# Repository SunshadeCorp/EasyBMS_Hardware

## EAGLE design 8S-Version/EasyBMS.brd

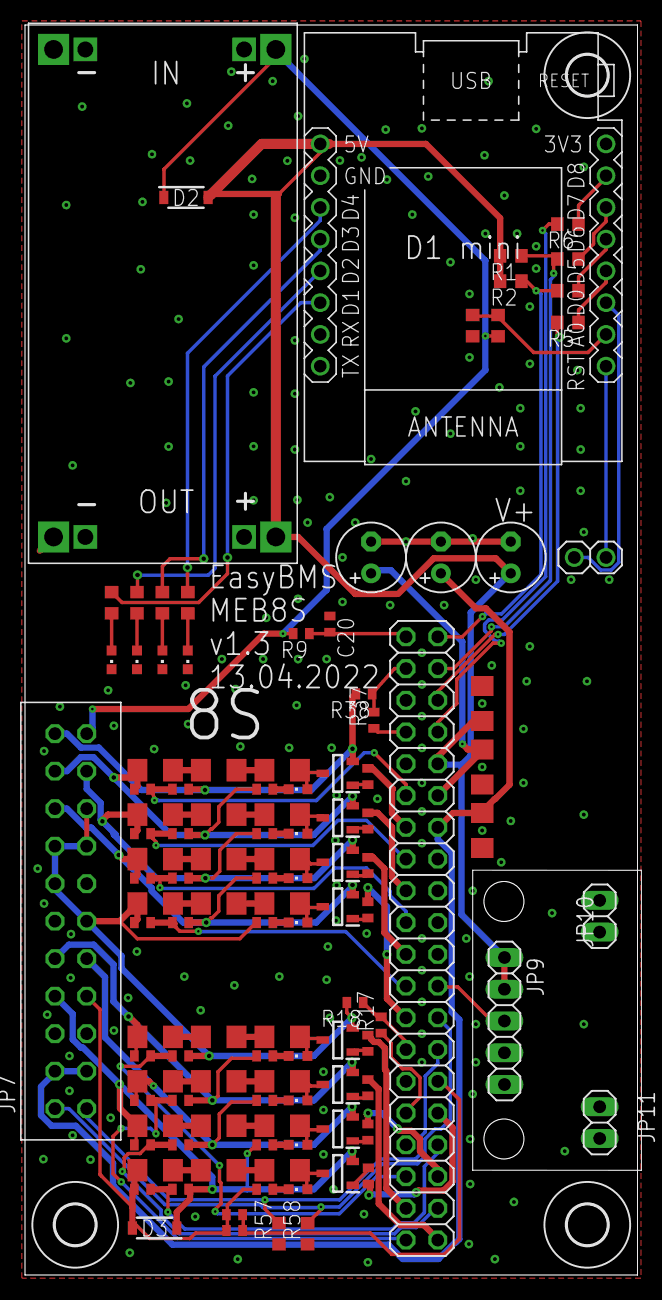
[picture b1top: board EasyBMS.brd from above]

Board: 2 copper layers, 49.0 x 100.0 mm, 117 parts (0 on the bottom side), 98 nets.

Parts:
C1, C2, C3: 1uF; E2,5-6
C4, C18, C19: 100nF; C1206
C5, C6, C7, C8, C9, C12, C13, C14, C15: 10nF; C0402
C20: 100n; C0402
D2, D3: SM4007PL-TP; SODFL3616X135N
H1, H2, H3: MOUNT-HOLE3.2; 3,2
JP3, JP10, JP11: 1X02
JP5: 2X20
JP7: 2X11_MEB12S
JP9: 1X05
LED1, LED2, LED3, LED4, LED5, LED6, LED7, LED8, LED12, LED13, LED14, LED15: KT-0603R; CHIPLED_0603
Q2, Q3, Q4, Q5, Q8, Q9, Q10, Q11: BSS84LT1G; SOT96P237X111-3N
R1, R2: 5K1; R0603
R3, R9, R12, R18, R24, R30, R36, R38, R64, R70, R76, R83: 100R; R0402
R4, R7, R8, R14, R20, R21, R25, R26, R27, R31, R32, R33, R49, R50, R51, R65, R66, R67, R71, R72, R73, R77, R78, R79: 10R0; R1206
R5, R6, R61, R62: 1k; R0603
R10, R22, R28, R34, R52, R68, R74, R80: 3.3k; R0402
R11, R23, R29, R35, R63, R69, R75, R81: 470R; R0402
R15: 470k; R0603
R16: 27K; R0603
R17, R37: 0R; R0402
R53, R54, R55, R56: 200R0; R0603
R57, R58: 12k; R0603
U$1: DC-DC-STEP-DOWN-LM2596HVS
U$2: WEMOS-D1-MINI

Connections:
5VDC: C3.+, C19.1, D2.2, JP5.10, JP9.1, JP9.2, R1.2, R2.2, U$1.OUT+, U$2.JP2.8
A0IN: R15.1, R16.2, U$2.JP1.2
C0: C5.1, JP5.30, R3.1
C1: C6.1, JP5.34, R12.1
C1+: C7.2, D3.1, JP7.16_C1+, Q2.2, R12.2, R14.1, R23.2
C1-: C5.2, C6.2, D3.2, JP7.15_TOTAL-, R3.2, R4.1, R11.2
C2: C7.1, JP5.38, R24.1
C2+: C9.2, JP7.13_C2+, Q3.2, R24.2, R31.1, R35.2
C3: C9.1, JP5.39, R36.1
C3+: C8.2, JP7.14_C3+, Q5.2, R25.1, R29.2, R36.2
C4: C8.1, JP5.35, R30.1
C4+: C12.2, JP7.5_C8+, JP7.7_C6+, JP7.8_C7+, JP7.10_C5+, JP7.11_C4+, Q4.2, R18.2, R30.2, R49.1, R63.2
C5: JP5.31, R17.1
C5+: C13.2, JP7.6_C9+, Q8.2, R64.2, R65.1, R69.2
C6: JP5.27, R17.2, R18.1
C6+: C14.2, JP7.3_C10+, Q9.2, R70.2, R71.1, R75.2
C7: C12.1, JP5.23, R64.1
C7+: C15.2, JP7.4_C11+, Q10.2, R76.2, R77.1, R81.2
C8: C13.1, JP5.19, R70.1
C8+: JP7.2_TOTAL+2, Q11.2, R38.2, R83.2
C9: C14.1, JP5.15, R76.1
C10: C15.1, JP5.11, R83.1
C11: JP5.7, R37.1
C12: JP5.3, R37.2, R38.1
CSB: JP5.8, R6.2
GND: C1.-, C2.-, C3.-, C4.2, C18.2, C19.2, C20.1, JP5.16, JP5.18, JP7.17_TOTAL-, JP9.4, JP9.5, JP10.1, JP10.2, JP11.1, JP11.2, LED1.C, LED2.C, LED3.C, LED4.C, R16.1, R57.1, R58.1, U$1.IN-, U$1.OUT-, U$2.JP2.7
ISIGNAL: JP5.24, JP9.3
MISO: JP5.2, R2.1, R61.2
MOSI: JP5.4, R1.1, R62.2
unnamed: LED1.A, R53.1
unnamed: LED2.A, R54.1
unnamed: LED3.A, R55.1
unnamed: LED4.A, R56.1
unnamed: JP3.2, U$2.JP1.1
unnamed: JP3.1, U$2.JP1.3
unnamed: R5.1, U$2.JP1.4
unnamed: R4.2, R7.1
unnamed: R7.2, R8.1
unnamed: LED5.A, Q2.3, R8.2
unnamed: Q2.1, R10.2
unnamed: LED5.C, R11.1
unnamed: R14.2, R20.1
unnamed: R20.2, R21.1
unnamed: R6.1, U$2.JP1.7
unnamed: LED6.A, Q3.3, R21.2
unnamed: Q3.1, R22.2
unnamed: LED6.C, R23.1
unnamed: R25.2, R26.1
unnamed: R26.2, R27.1
unnamed: LED7.A, Q4.3, R27.2
unnamed: Q4.1, R28.2
unnamed: LED7.C, R29.1
unnamed: R31.2, R32.1
unnamed: R32.2, R33.1
unnamed: LED8.A, Q5.3, R33.2
unnamed: R56.2, U$2.JP2.6
unnamed: Q5.1, R34.2
unnamed: LED8.C, R35.1
unnamed: R49.2, R50.1
unnamed: R50.2, R51.1
unnamed: LED12.A, Q8.3, R51.2
unnamed: Q8.1, R52.2
unnamed: LED12.C, R63.1
unnamed: R65.2, R66.1
unnamed: R66.2, R67.1
unnamed: LED13.A, Q9.3, R67.2
unnamed: Q9.1, R68.2
unnamed: LED13.C, R69.1
unnamed: R71.2, R72.1
unnamed: R72.2, R73.1
unnamed: LED14.A, Q10.3, R73.2
unnamed: Q10.1, R74.2
unnamed: LED14.C, R75.1
unnamed: R77.2, R78.1
unnamed: R78.2, R79.1
unnamed: LED15.A, Q11.3, R79.2
unnamed: Q11.1, R80.2
unnamed: LED15.C, R81.1
unnamed: R53.2, U$2.JP2.3
unnamed: R61.1, U$2.JP1.5
unnamed: R62.1, U$2.JP1.6
unnamed: R55.2, U$2.JP2.5
unnamed: R54.2, U$2.JP2.4
S1: JP5.32, R10.1
S2: JP5.36, R22.1
S3: JP5.40, R34.1
S4: JP5.37, R28.1
S7: JP5.25, R52.1
S8: JP5.21, R68.1
S9: JP5.17, R74.1
S10: JP5.13, R80.1
SCK: JP5.6, R5.2
V+: C20.2, JP5.1, R9.1
VIN: D2.1, JP7.1_TOTAL+, R9.2, R15.2, U$1.IN+
VREF1: C1.+, C18.1, JP5.12
VREF2: C2.+, C4.1, JP5.14, JP7.19_THERMO1_IN, JP7.20_THERMO2_IN
VTEMP1: JP5.28, JP7.21_THERMO1_OUT, R57.2
VTEMP2: JP5.26, JP7.22_THERMO2_OUT, R58.2

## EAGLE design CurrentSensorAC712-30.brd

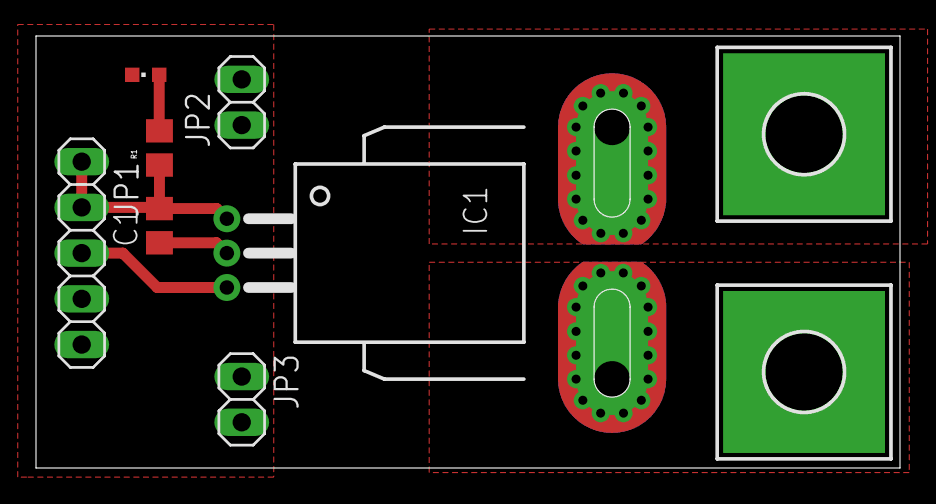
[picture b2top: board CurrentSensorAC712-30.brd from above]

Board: 2 copper layers, 48.0 x 24.0 mm, 9 parts (0 on the bottom side), 6 nets.

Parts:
C1: 100nF; C0805
H1, H2: MOUNT-PAD-SQUARE4.3; 4,3-PAD-SQUARE
IC1: ACS758LCB-050B-PFF-T; CB-PFF
JP1: 1X05
JP2, JP3: 1X02
LED1: KT-0603R; CHIPLED_0603
R1: 1k; R0805

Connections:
5VDC: C1.2, IC1.1, JP1.1, JP1.2, R1.1
GND: C1.1, IC1.2, JP1.4, JP1.5, JP2.1, JP2.2, JP3.1, JP3.2, LED1.C
IN: H1.B4,3, IC1.IP+, IC1.IP+@2, IC1.IP+@3, IC1.IP+@4, IC1.IP+@5, IC1.IP+@6, IC1.IP+@7, IC1.IP+@8, IC1.IP+@9, IC1.IP+@10, IC1.IP+@11, IC1.IP+@12, IC1.IP+@13, IC1.IP+@14, IC1.IP+@15, IC1.IP+@16, IC1.IP+@17
unnamed: LED1.A, R1.2
unnamed: IC1.3, JP1.3
OUT: H2.B4,3, IC1.IP-, IC1.IP-@2, IC1.IP-@3, IC1.IP-@4, IC1.IP-@5, IC1.IP-@6, IC1.IP-@7, IC1.IP-@8, IC1.IP-@9, IC1.IP-@10, IC1.IP-@11, IC1.IP-@12, IC1.IP-@13, IC1.IP-@14, IC1.IP-@15, IC1.IP-@16, IC1.IP-@17

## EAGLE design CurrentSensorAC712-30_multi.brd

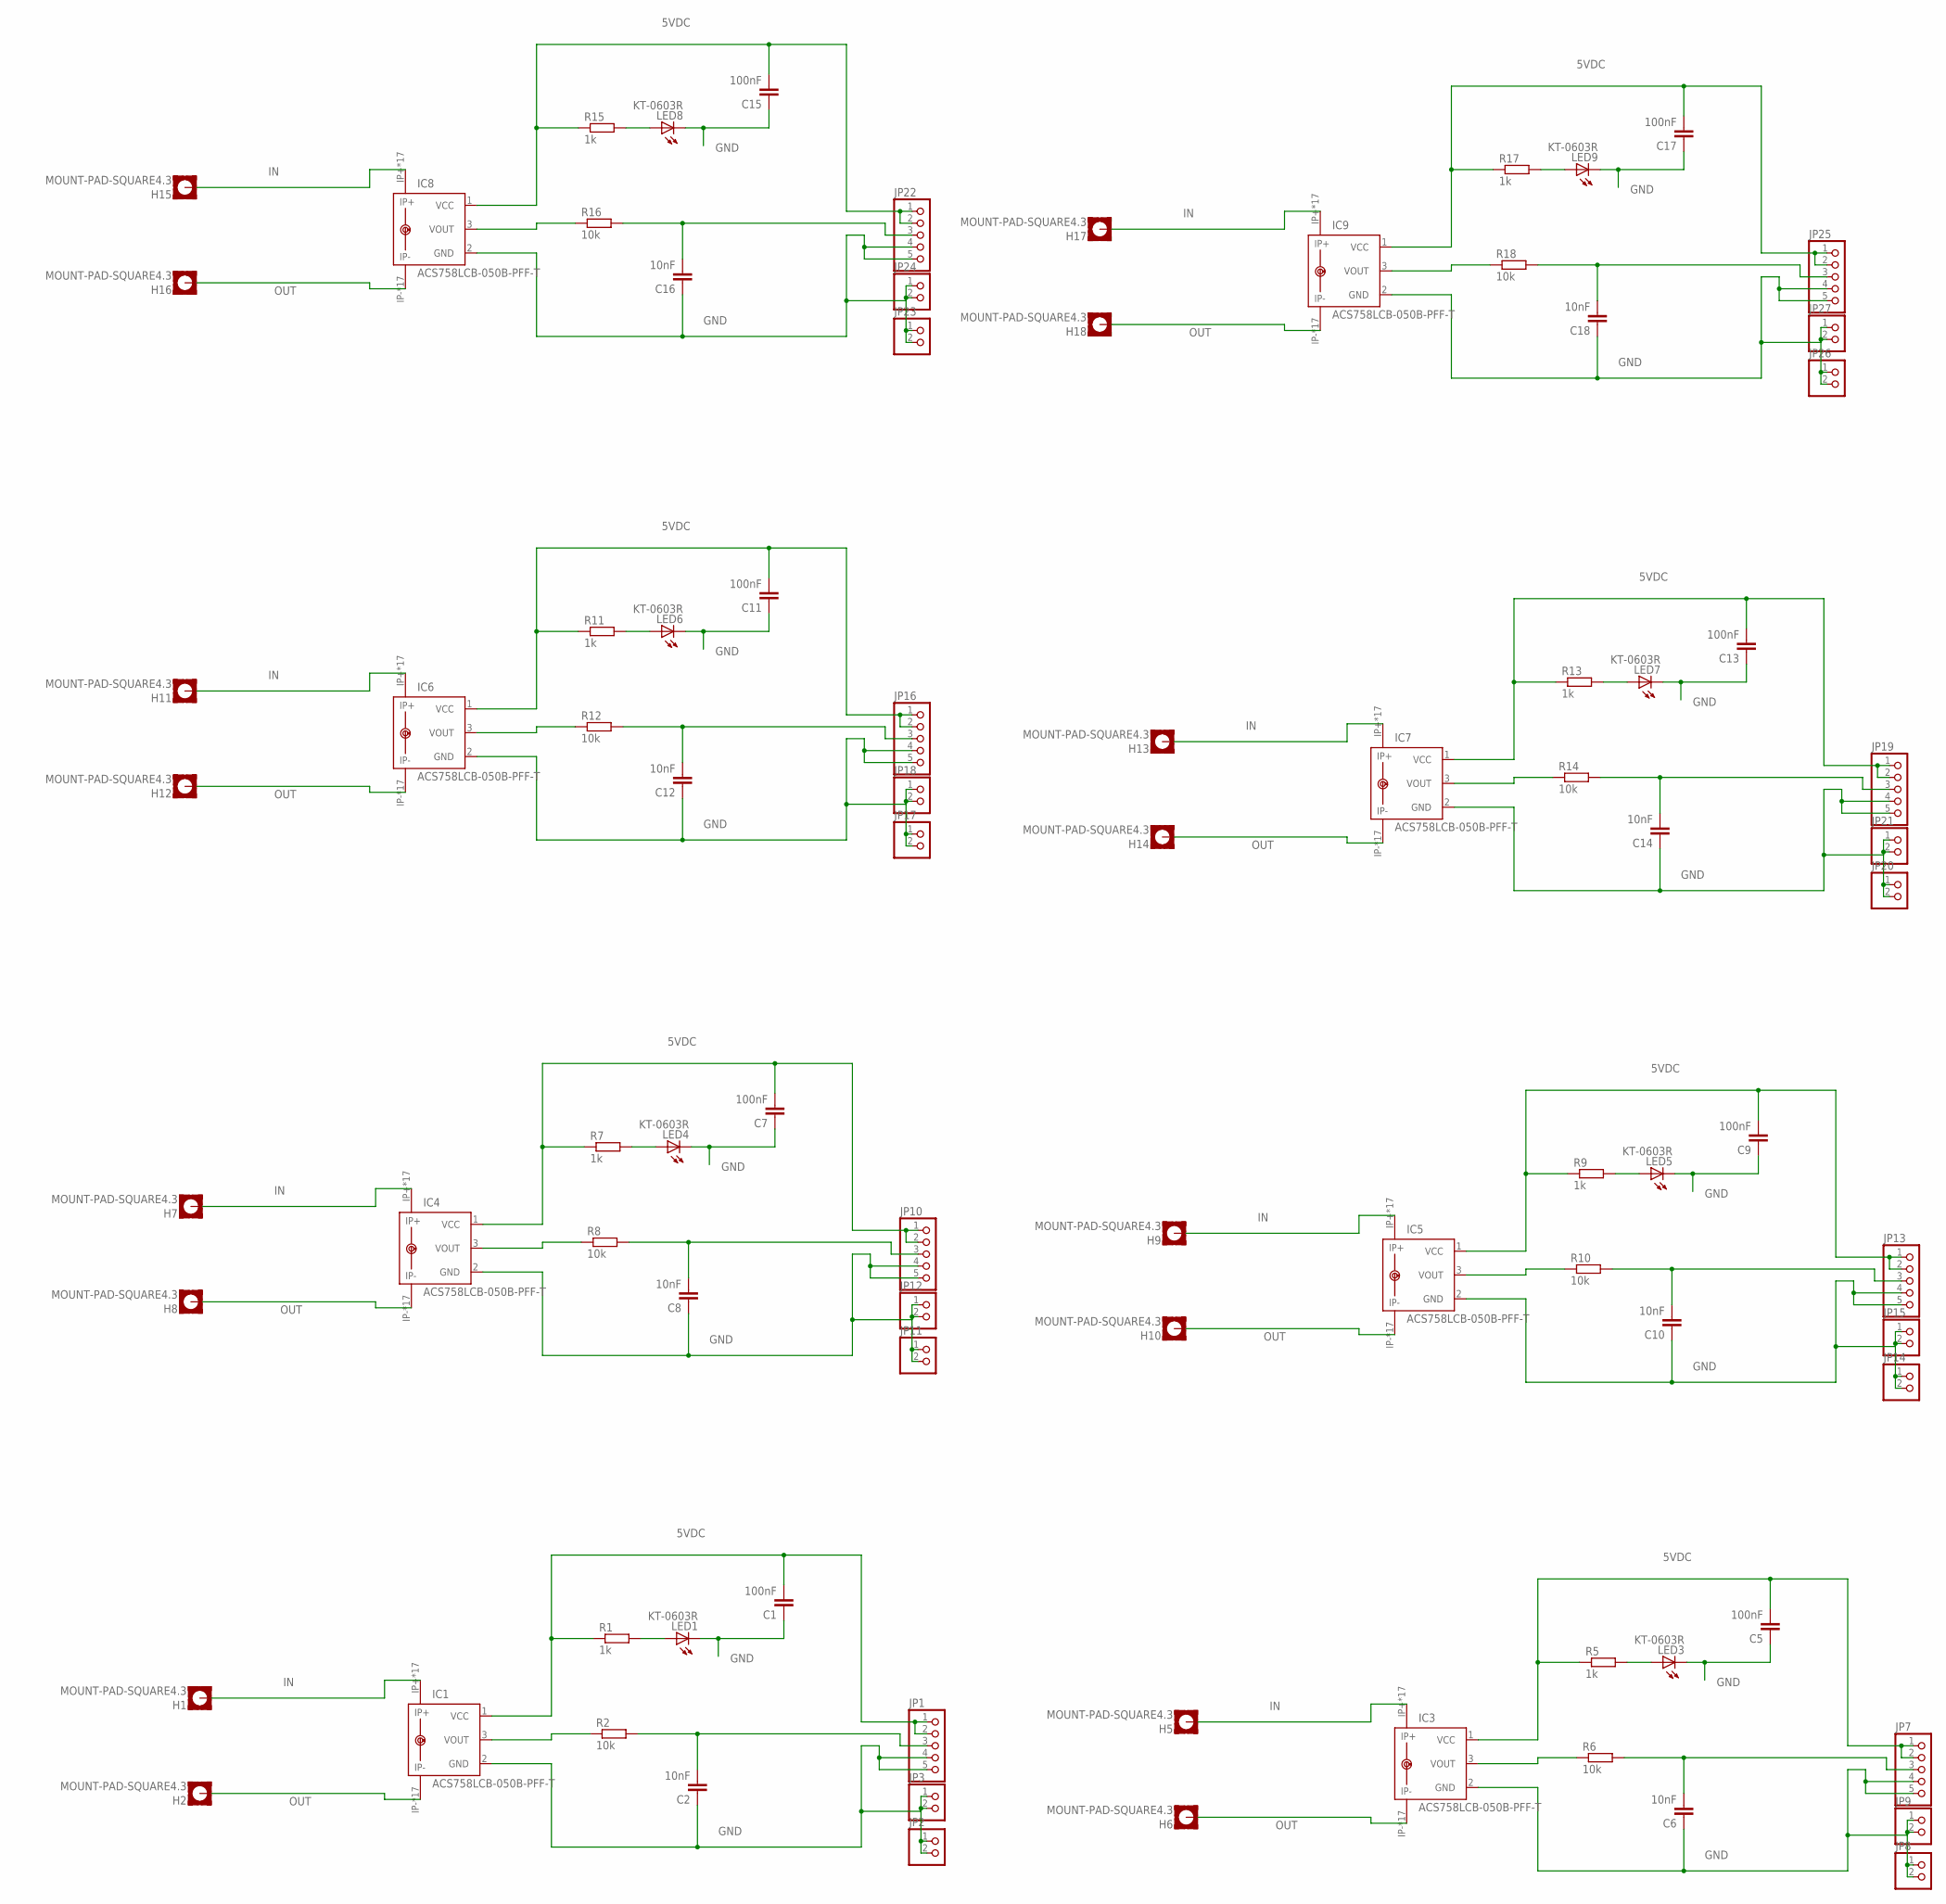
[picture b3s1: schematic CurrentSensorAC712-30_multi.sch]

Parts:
C1, C5, C7, C9, C11, C13, C15, C17: 100nF; C0805
C2, C6, C8, C10, C12, C14, C16, C18: 10nF; C0805
H1, H2, H5, H6, H7, H8, H9, H10, H11, H12, H13, H14, H15, H16, H17, H18: MOUNT-PAD-SQUARE4.3; 4,3-PAD-SQUARE
IC1, IC3, IC4, IC5, IC6, IC7, IC8, IC9: ACS758LCB-050B-PFF-T; CB-PFF
JP1, JP7, JP10, JP13, JP16, JP19, JP22, JP25: PINHD-1X5; 1X05
JP2, JP3, JP8, JP9, JP11, JP12, JP14, JP15, JP17, JP18, JP20, JP21, JP23, JP24, JP26, JP27: PINHD-1X2; 1X02
LED1, LED3, LED4, LED5, LED6, LED7, LED8, LED9: KT-0603R; CHIPLED_0603
R1, R5, R7, R9, R11, R13, R15, R17: 1k; R0805
R2, R6, R8, R10, R12, R14, R16, R18: 10k; R0805

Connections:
5VDC: C1.2, C5.2, C7.2, C9.2, C11.2, C13.2, C15.2, C17.2, IC1.1 (VCC), IC3.1 (VCC), IC4.1 (VCC), IC5.1 (VCC), IC6.1 (VCC), IC7.1 (VCC), IC8.1 (VCC), IC9.1 (VCC), JP1.1, JP1.2, JP7.1, JP7.2, JP10.1, JP10.2, JP13.1, JP13.2, JP16.1, JP16.2, JP19.1, JP19.2, JP22.1, JP22.2, JP25.1, JP25.2, R1.1, R5.1, R7.1, R9.1, R11.1, R13.1, R15.1, R17.1
GND: C1.1, C2.1, C5.1, C6.1, C7.1, C8.1, C9.1, C10.1, C11.1, C12.1, C13.1, C14.1, C15.1, C16.1, C17.1, C18.1, IC1.2 (GND), IC3.2 (GND), IC4.2 (GND), IC5.2 (GND), IC6.2 (GND), IC7.2 (GND), IC8.2 (GND), IC9.2 (GND), JP1.4, JP1.5, JP2.1, JP2.2, JP3.1, JP3.2, JP7.4, JP7.5, JP8.1, JP8.2, JP9.1, JP9.2, JP10.4, JP10.5, JP11.1, JP11.2, JP12.1, JP12.2, JP13.4, JP13.5, JP14.1, JP14.2, JP15.1, JP15.2, JP16.4, JP16.5, JP17.1, JP17.2, JP18.1, JP18.2, JP19.4, JP19.5, JP20.1, JP20.2, JP21.1, JP21.2, JP22.4, JP22.5, JP23.1, JP23.2, JP24.1, JP24.2, JP25.4, JP25.5, JP26.1, JP26.2, JP27.1, JP27.2, LED1.C, LED3.C, LED4.C, LED5.C, LED6.C, LED7.C, LED8.C, LED9.C
IN: H1.B4,3, H5.B4,3, H7.B4,3, H9.B4,3, H11.B4,3, H13.B4,3, H15.B4,3, H17.B4,3, IC1.IP+, IC1.IP+@2 (IP+), IC1.IP+@3 (IP+), IC1.IP+@4 (IP+), IC1.IP+@5 (IP+), IC1.IP+@6 (IP+), IC1.IP+@7 (IP+), IC1.IP+@8 (IP+), IC1.IP+@9 (IP+), IC1.IP+@10 (IP+), IC1.IP+@11 (IP+), IC1.IP+@12 (IP+), IC1.IP+@13 (IP+), IC1.IP+@14 (IP+), IC1.IP+@15 (IP+), IC1.IP+@16 (IP+), IC1.IP+@17 (IP+), IC3.IP+, IC3.IP+@2 (IP+), IC3.IP+@3 (IP+), IC3.IP+@4 (IP+), IC3.IP+@5 (IP+), IC3.IP+@6 (IP+), IC3.IP+@7 (IP+), IC3.IP+@8 (IP+), IC3.IP+@9 (IP+), IC3.IP+@10 (IP+), IC3.IP+@11 (IP+), IC3.IP+@12 (IP+), IC3.IP+@13 (IP+), IC3.IP+@14 (IP+), IC3.IP+@15 (IP+), IC3.IP+@16 (IP+), IC3.IP+@17 (IP+), IC4.IP+, IC4.IP+@2 (IP+), IC4.IP+@3 (IP+), IC4.IP+@4 (IP+), IC4.IP+@5 (IP+), IC4.IP+@6 (IP+), IC4.IP+@7 (IP+), IC4.IP+@8 (IP+), IC4.IP+@9 (IP+), IC4.IP+@10 (IP+), IC4.IP+@11 (IP+), IC4.IP+@12 (IP+), IC4.IP+@13 (IP+), IC4.IP+@14 (IP+), IC4.IP+@15 (IP+), IC4.IP+@16 (IP+), IC4.IP+@17 (IP+), IC5.IP+, IC5.IP+@2 (IP+), IC5.IP+@3 (IP+), IC5.IP+@4 (IP+), IC5.IP+@5 (IP+), IC5.IP+@6 (IP+), IC5.IP+@7 (IP+), IC5.IP+@8 (IP+), IC5.IP+@9 (IP+), IC5.IP+@10 (IP+), IC5.IP+@11 (IP+), IC5.IP+@12 (IP+), IC5.IP+@13 (IP+), IC5.IP+@14 (IP+), IC5.IP+@15 (IP+), IC5.IP+@16 (IP+), IC5.IP+@17 (IP+), IC6.IP+, IC6.IP+@2 (IP+), IC6.IP+@3 (IP+), IC6.IP+@4 (IP+), IC6.IP+@5 (IP+), IC6.IP+@6 (IP+), IC6.IP+@7 (IP+), IC6.IP+@8 (IP+), IC6.IP+@9 (IP+), IC6.IP+@10 (IP+), IC6.IP+@11 (IP+), IC6.IP+@12 (IP+), IC6.IP+@13 (IP+), IC6.IP+@14 (IP+), IC6.IP+@15 (IP+), IC6.IP+@16 (IP+), IC6.IP+@17 (IP+), IC7.IP+, IC7.IP+@2 (IP+), IC7.IP+@3 (IP+), IC7.IP+@4 (IP+), IC7.IP+@5 (IP+), IC7.IP+@6 (IP+), IC7.IP+@7 (IP+), IC7.IP+@8 (IP+), IC7.IP+@9 (IP+), IC7.IP+@10 (IP+), IC7.IP+@11 (IP+), IC7.IP+@12 (IP+), IC7.IP+@13 (IP+), IC7.IP+@14 (IP+), IC7.IP+@15 (IP+), IC7.IP+@16 (IP+), IC7.IP+@17 (IP+), IC8.IP+, IC8.IP+@2 (IP+), IC8.IP+@3 (IP+), IC8.IP+@4 (IP+), IC8.IP+@5 (IP+), IC8.IP+@6 (IP+), IC8.IP+@7 (IP+), IC8.IP+@8 (IP+), IC8.IP+@9 (IP+), IC8.IP+@10 (IP+), IC8.IP+@11 (IP+), IC8.IP+@12 (IP+), IC8.IP+@13 (IP+), IC8.IP+@14 (IP+), IC8.IP+@15 (IP+), IC8.IP+@16 (IP+), IC8.IP+@17 (IP+), IC9.IP+, IC9.IP+@2 (IP+), IC9.IP+@3 (IP+), IC9.IP+@4 (IP+), IC9.IP+@5 (IP+), IC9.IP+@6 (IP+), IC9.IP+@7 (IP+), IC9.IP+@8 (IP+), IC9.IP+@9 (IP+), IC9.IP+@10 (IP+), IC9.IP+@11 (IP+), IC9.IP+@12 (IP+), IC9.IP+@13 (IP+), IC9.IP+@14 (IP+), IC9.IP+@15 (IP+), IC9.IP+@16 (IP+), IC9.IP+@17 (IP+)
unnamed: IC1.3 (VOUT), R2.1
unnamed: LED1.A, R1.2
unnamed: C2.2, JP1.3, R2.2
unnamed: LED3.A, R5.2
unnamed: C6.2, JP7.3, R6.2
unnamed: IC3.3 (VOUT), R6.1
unnamed: LED4.A, R7.2
unnamed: C8.2, JP10.3, R8.2
unnamed: IC4.3 (VOUT), R8.1
unnamed: LED5.A, R9.2
unnamed: C10.2, JP13.3, R10.2
unnamed: IC5.3 (VOUT), R10.1
unnamed: LED6.A, R11.2
unnamed: C12.2, JP16.3, R12.2
unnamed: IC6.3 (VOUT), R12.1
unnamed: LED7.A, R13.2
unnamed: C14.2, JP19.3, R14.2
unnamed: IC7.3 (VOUT), R14.1
unnamed: LED8.A, R15.2
unnamed: C16.2, JP22.3, R16.2
unnamed: IC8.3 (VOUT), R16.1
unnamed: LED9.A, R17.2
unnamed: C18.2, JP25.3, R18.2
unnamed: IC9.3 (VOUT), R18.1
OUT: H2.B4,3, H6.B4,3, H8.B4,3, H10.B4,3, H12.B4,3, H14.B4,3, H16.B4,3, H18.B4,3, IC1.IP-, IC1.IP-@2 (IP-), IC1.IP-@3 (IP-), IC1.IP-@4 (IP-), IC1.IP-@5 (IP-), IC1.IP-@6 (IP-), IC1.IP-@7 (IP-), IC1.IP-@8 (IP-), IC1.IP-@9 (IP-), IC1.IP-@10 (IP-), IC1.IP-@11 (IP-), IC1.IP-@12 (IP-), IC1.IP-@13 (IP-), IC1.IP-@14 (IP-), IC1.IP-@15 (IP-), IC1.IP-@16 (IP-), IC1.IP-@17 (IP-), IC3.IP-, IC3.IP-@2 (IP-), IC3.IP-@3 (IP-), IC3.IP-@4 (IP-), IC3.IP-@5 (IP-), IC3.IP-@6 (IP-), IC3.IP-@7 (IP-), IC3.IP-@8 (IP-), IC3.IP-@9 (IP-), IC3.IP-@10 (IP-), IC3.IP-@11 (IP-), IC3.IP-@12 (IP-), IC3.IP-@13 (IP-), IC3.IP-@14 (IP-), IC3.IP-@15 (IP-), IC3.IP-@16 (IP-), IC3.IP-@17 (IP-), IC4.IP-, IC4.IP-@2 (IP-), IC4.IP-@3 (IP-), IC4.IP-@4 (IP-), IC4.IP-@5 (IP-), IC4.IP-@6 (IP-), IC4.IP-@7 (IP-), IC4.IP-@8 (IP-), IC4.IP-@9 (IP-), IC4.IP-@10 (IP-), IC4.IP-@11 (IP-), IC4.IP-@12 (IP-), IC4.IP-@13 (IP-), IC4.IP-@14 (IP-), IC4.IP-@15 (IP-), IC4.IP-@16 (IP-), IC4.IP-@17 (IP-), IC5.IP-, IC5.IP-@2 (IP-), IC5.IP-@3 (IP-), IC5.IP-@4 (IP-), IC5.IP-@5 (IP-), IC5.IP-@6 (IP-), IC5.IP-@7 (IP-), IC5.IP-@8 (IP-), IC5.IP-@9 (IP-), IC5.IP-@10 (IP-), IC5.IP-@11 (IP-), IC5.IP-@12 (IP-), IC5.IP-@13 (IP-), IC5.IP-@14 (IP-), IC5.IP-@15 (IP-), IC5.IP-@16 (IP-), IC5.IP-@17 (IP-), IC6.IP-, IC6.IP-@2 (IP-), IC6.IP-@3 (IP-), IC6.IP-@4 (IP-), IC6.IP-@5 (IP-), IC6.IP-@6 (IP-), IC6.IP-@7 (IP-), IC6.IP-@8 (IP-), IC6.IP-@9 (IP-), IC6.IP-@10 (IP-), IC6.IP-@11 (IP-), IC6.IP-@12 (IP-), IC6.IP-@13 (IP-), IC6.IP-@14 (IP-), IC6.IP-@15 (IP-), IC6.IP-@16 (IP-), IC6.IP-@17 (IP-), IC7.IP-, IC7.IP-@2 (IP-), IC7.IP-@3 (IP-), IC7.IP-@4 (IP-), IC7.IP-@5 (IP-), IC7.IP-@6 (IP-), IC7.IP-@7 (IP-), IC7.IP-@8 (IP-), IC7.IP-@9 (IP-), IC7.IP-@10 (IP-), IC7.IP-@11 (IP-), IC7.IP-@12 (IP-), IC7.IP-@13 (IP-), IC7.IP-@14 (IP-), IC7.IP-@15 (IP-), IC7.IP-@16 (IP-), IC7.IP-@17 (IP-), IC8.IP-, IC8.IP-@2 (IP-), IC8.IP-@3 (IP-), IC8.IP-@4 (IP-), IC8.IP-@5 (IP-), IC8.IP-@6 (IP-), IC8.IP-@7 (IP-), IC8.IP-@8 (IP-), IC8.IP-@9 (IP-), IC8.IP-@10 (IP-), IC8.IP-@11 (IP-), IC8.IP-@12 (IP-), IC8.IP-@13 (IP-), IC8.IP-@14 (IP-), IC8.IP-@15 (IP-), IC8.IP-@16 (IP-), IC8.IP-@17 (IP-), IC9.IP-, IC9.IP-@2 (IP-), IC9.IP-@3 (IP-), IC9.IP-@4 (IP-), IC9.IP-@5 (IP-), IC9.IP-@6 (IP-), IC9.IP-@7 (IP-), IC9.IP-@8 (IP-), IC9.IP-@9 (IP-), IC9.IP-@10 (IP-), IC9.IP-@11 (IP-), IC9.IP-@12 (IP-), IC9.IP-@13 (IP-), IC9.IP-@14 (IP-), IC9.IP-@15 (IP-), IC9.IP-@16 (IP-), IC9.IP-@17 (IP-)

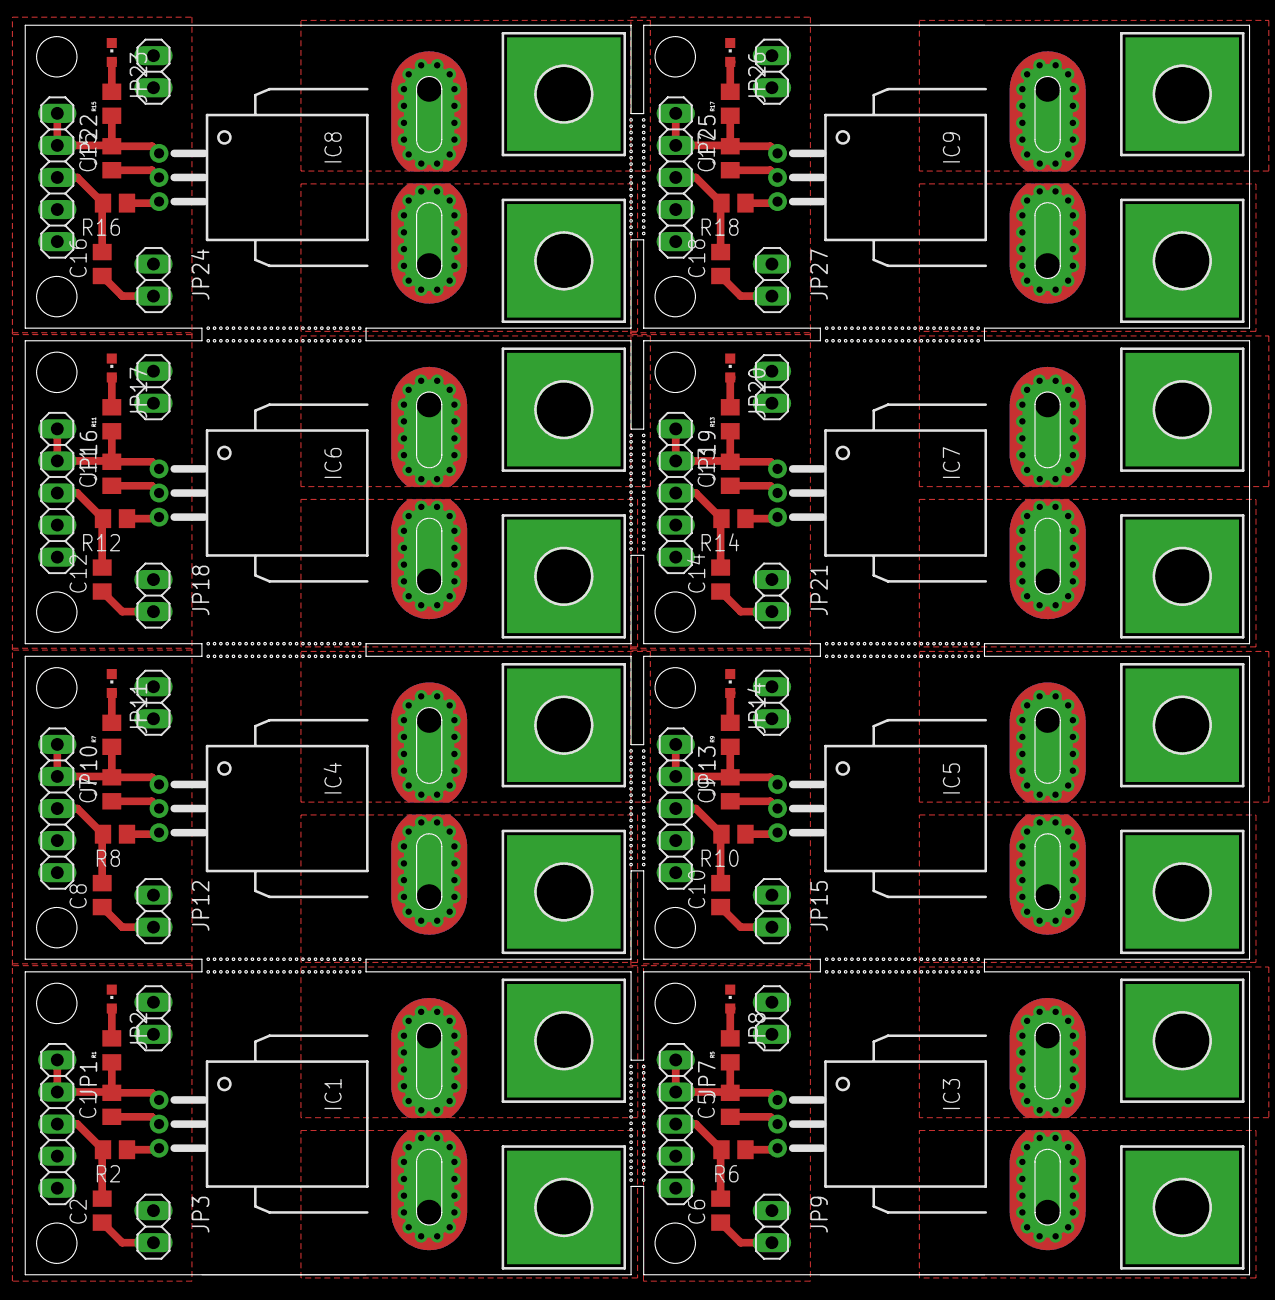
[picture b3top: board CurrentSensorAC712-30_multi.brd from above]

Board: 2 copper layers, 97.0 x 99.0 mm, 88 parts (0 on the bottom side), 28 nets.

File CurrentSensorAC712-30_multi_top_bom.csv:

Comment,Designator,Footprint,LCSC Part #
1k,R1 R5 R7 R9 R11 R13 R15 R17,R0805,
10k,R2 R6 R8 R10 R12 R14 R16 R18,R0805,
10nF,C2 C6 C8 C10 C12 C14 C16 C18,C0805,
100nF,C1 C5 C7 C9 C11 C13 C15 C17,C0805,
KT-0603R,LED1 LED3 LED4 LED5 LED6 LED7 LED8 LED9,CHIPLED_0603,

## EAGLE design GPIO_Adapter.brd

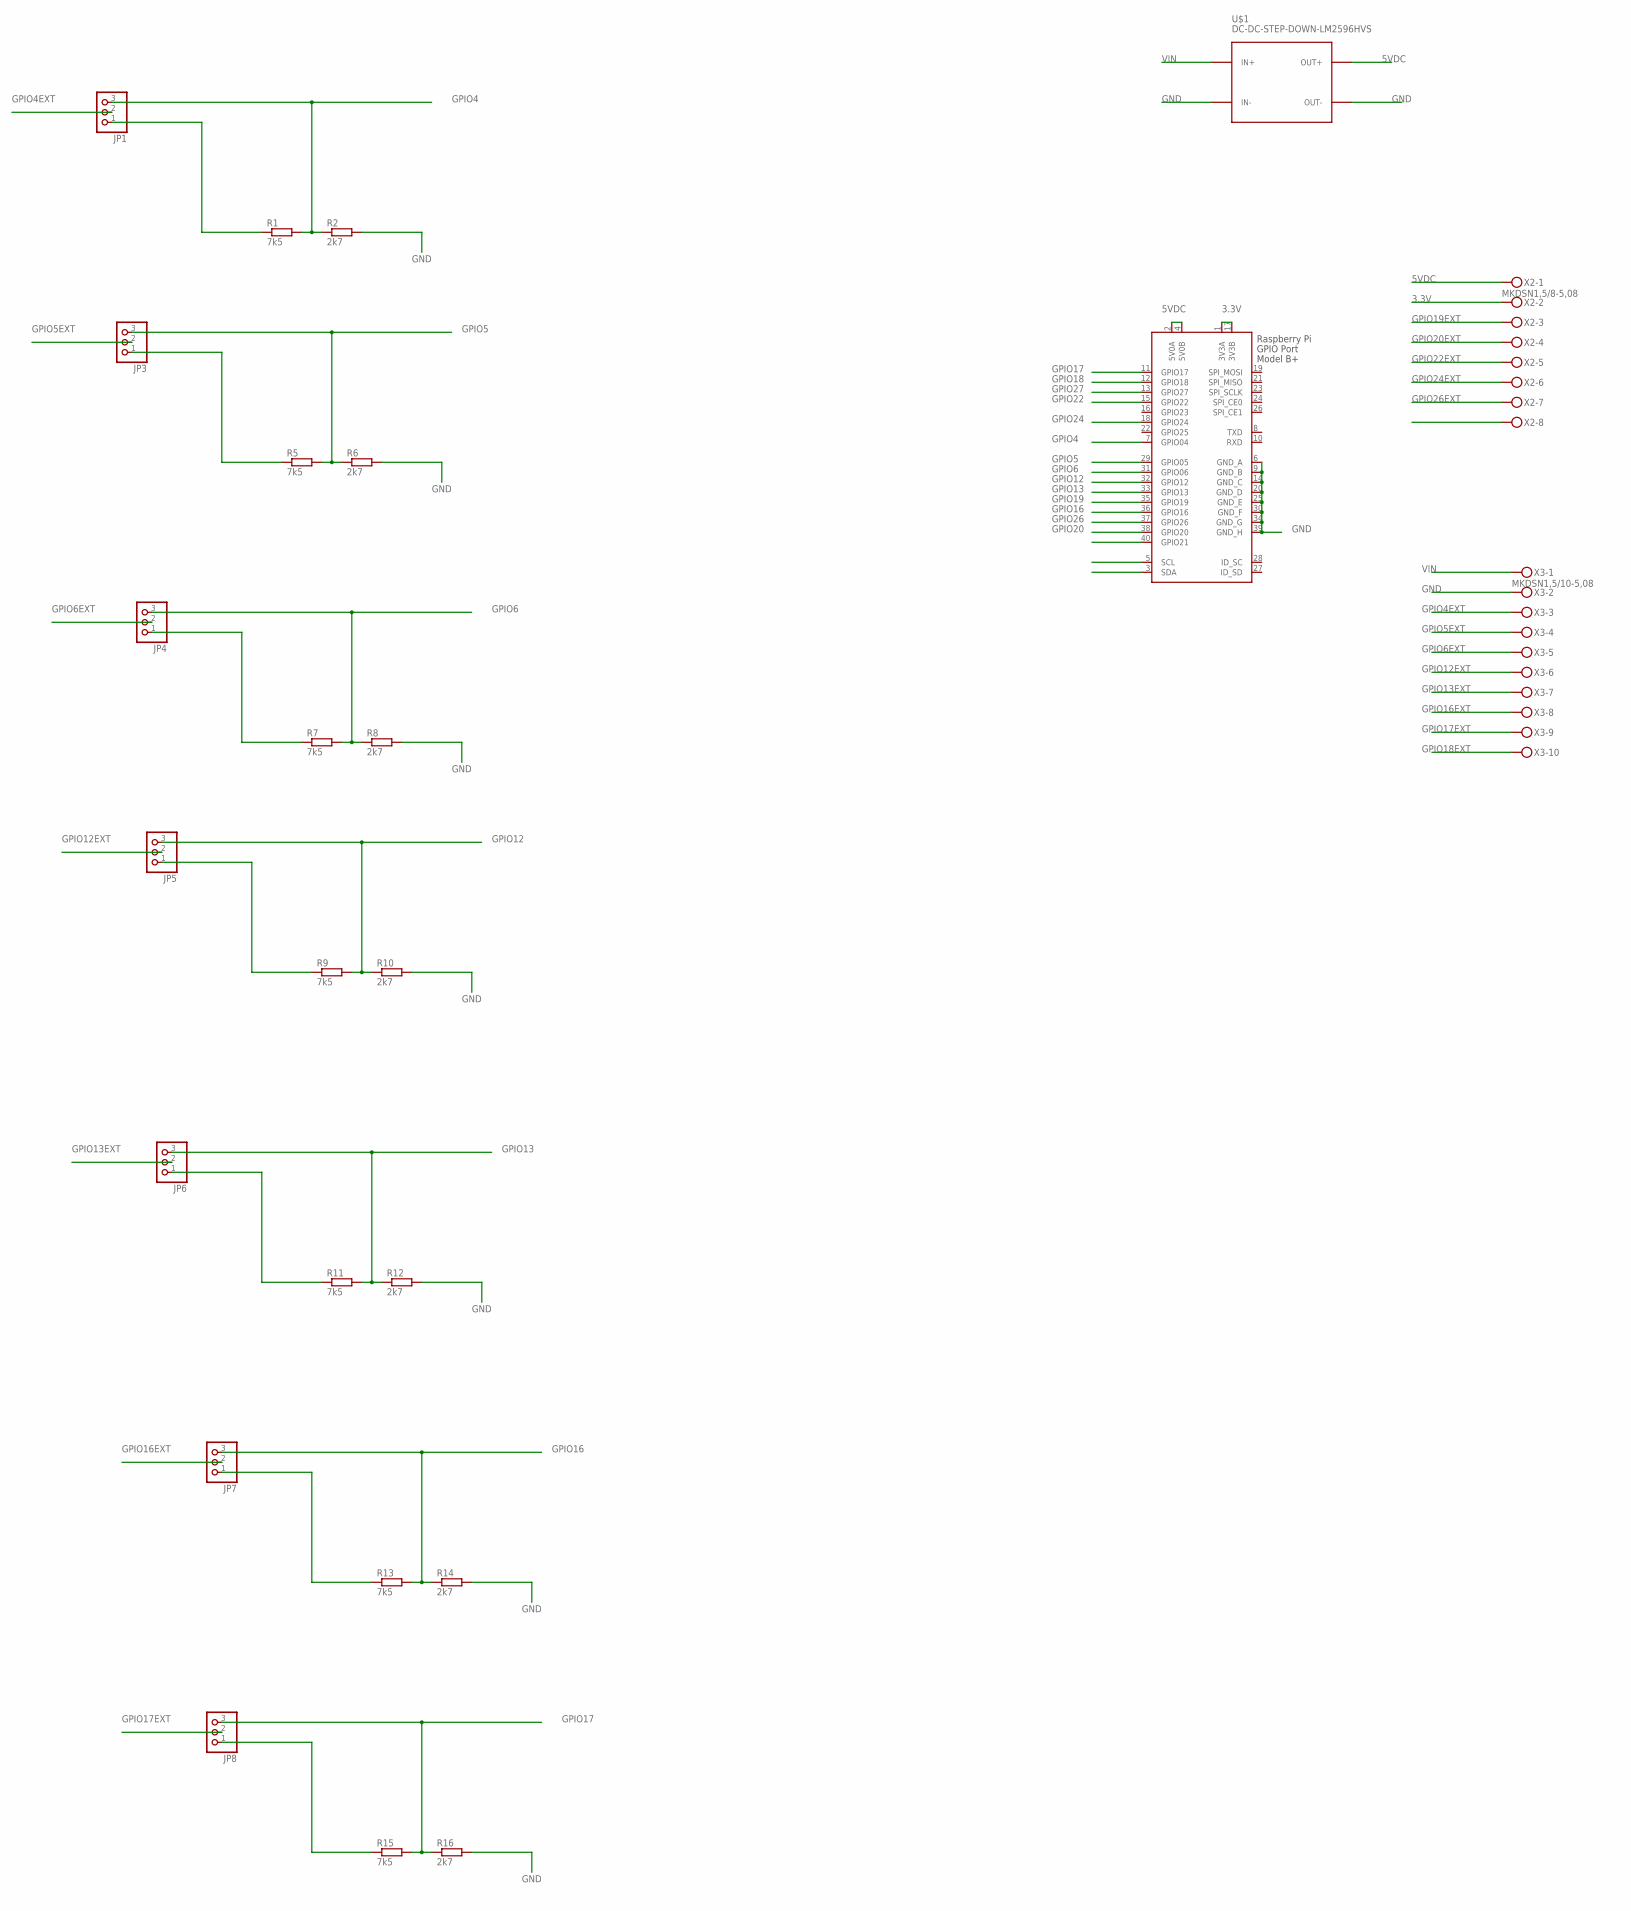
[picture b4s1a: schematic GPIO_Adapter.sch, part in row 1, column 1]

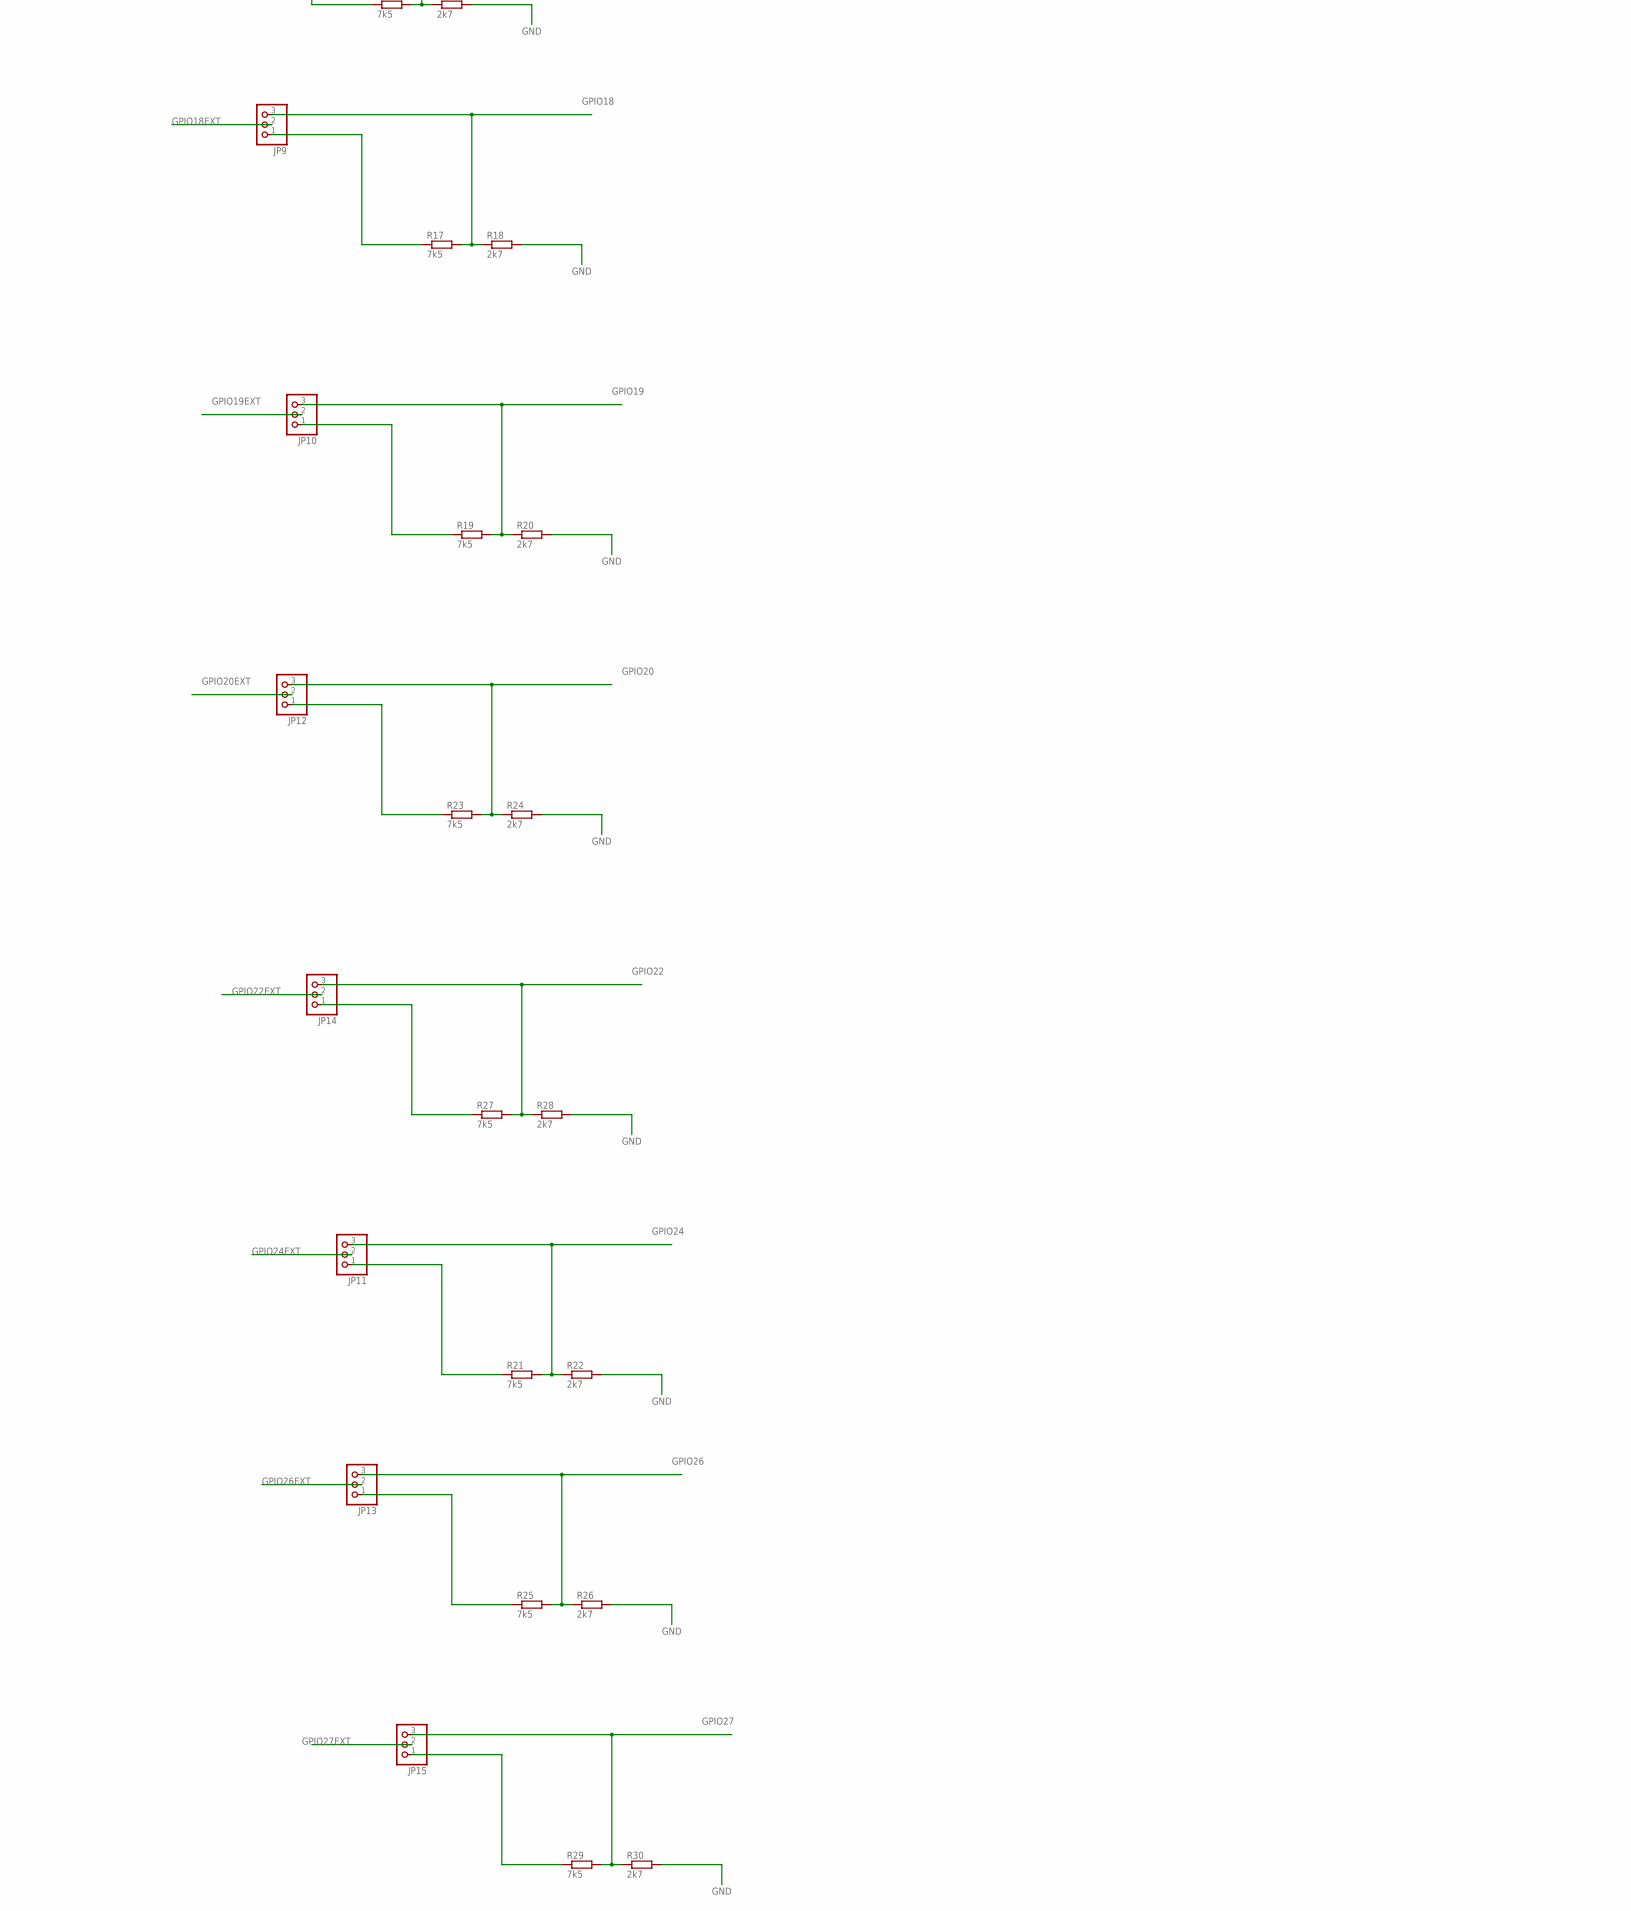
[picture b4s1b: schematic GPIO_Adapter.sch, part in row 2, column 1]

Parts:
JP1, JP3, JP4, JP5, JP6, JP7, JP8, JP9, JP10, JP11, JP12, JP13, JP14, JP15: PINHD-1X3; 1X03
R1, R5, R7, R9, R11, R13, R15, R17, R19, R21, R23, R25, R27, R29: 7k5; R0805
R2, R6, R8, R10, R12, R14, R16, R18, R20, R22, R24, R26, R28, R30: 2k7; R0805
U$1: DC-DC-STEP-DOWN-LM2596HVS
X1: RASPI_BOARD_B+#_F; RASPI_BOARD_B+_FULL
X2: MKDSN1,5/8-5,08
X3: MKDSN1,5/10-5,08

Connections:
3.3V: X1.1 (3V3A), X1.17 (3V3B), X2.2
5VDC: U$1.OUT+, X1.2 (5V0A), X1.4 (5V0B), X2.1
GND: R2.2, R6.2, R8.2, R10.2, R12.2, R14.2, R16.2, R18.2, R20.2, R22.2, R24.2, R26.2, R28.2, R30.2, U$1.IN-, U$1.OUT-, X1.6 (GND_A), X1.9 (GND_B), X1.14 (GND_C), X1.20 (GND_D), X1.25 (GND_E), X1.30 (GND_F), X1.34 (GND_G), X1.39 (GND_H), X3.2
GPIO4: JP1.3, R1.2, R2.1, X1.7 (GPIO04)
GPIO4EXT: JP1.2, X3.3
GPIO5: JP3.3, R5.2, R6.1, X1.29 (GPIO05)
GPIO5EXT: JP3.2, X3.4
GPIO6: JP4.3, R7.2, R8.1, X1.31 (GPIO06)
GPIO6EXT: JP4.2, X3.5
GPIO12: JP5.3, R9.2, R10.1, X1.32 (GPIO12)
GPIO12EXT: JP5.2, X3.6
GPIO13: JP6.3, R11.2, R12.1, X1.33 (GPIO13)
GPIO13EXT: JP6.2, X3.7
GPIO16: JP7.3, R13.2, R14.1, X1.36 (GPIO16)
GPIO16EXT: JP7.2, X3.8
GPIO17: JP8.3, R15.2, R16.1, X1.11 (GPIO17)
GPIO17EXT: JP8.2, X3.9
GPIO18: JP9.3, R17.2, R18.1, X1.12 (GPIO18)
GPIO18EXT: JP9.2, X3.10
GPIO19: JP10.3, R19.2, R20.1, X1.35 (GPIO19)
GPIO19EXT: JP10.2, X2.3
GPIO20: JP12.3, R23.2, R24.1, X1.38 (GPIO20)
GPIO20EXT: JP12.2, X2.4
GPIO22: JP14.3, R27.2, R28.1, X1.15 (GPIO22)
GPIO22EXT: JP14.2, X2.5
GPIO24: JP11.3, R21.2, R22.1, X1.18 (GPIO24)
GPIO24EXT: JP11.2, X2.6
GPIO26: JP13.3, R25.2, R26.1, X1.37 (GPIO26)
GPIO26EXT: JP13.2, X2.7
GPIO27: JP15.3, R29.2, R30.1, X1.13 (GPIO27)
GPIO27EXT: JP15.2, X2.8
unnamed: JP1.1, R1.1
unnamed: JP3.1, R5.1
unnamed: JP4.1, R7.1
unnamed: JP5.1, R9.1
unnamed: JP6.1, R11.1
unnamed: JP7.1, R13.1
unnamed: JP8.1, R15.1
unnamed: JP9.1, R17.1
unnamed: JP10.1, R19.1
unnamed: JP11.1, R21.1
unnamed: JP12.1, R23.1
unnamed: JP13.1, R25.1
unnamed: JP14.1, R27.1
unnamed: JP15.1, R29.1
VIN: U$1.IN+, X3.1

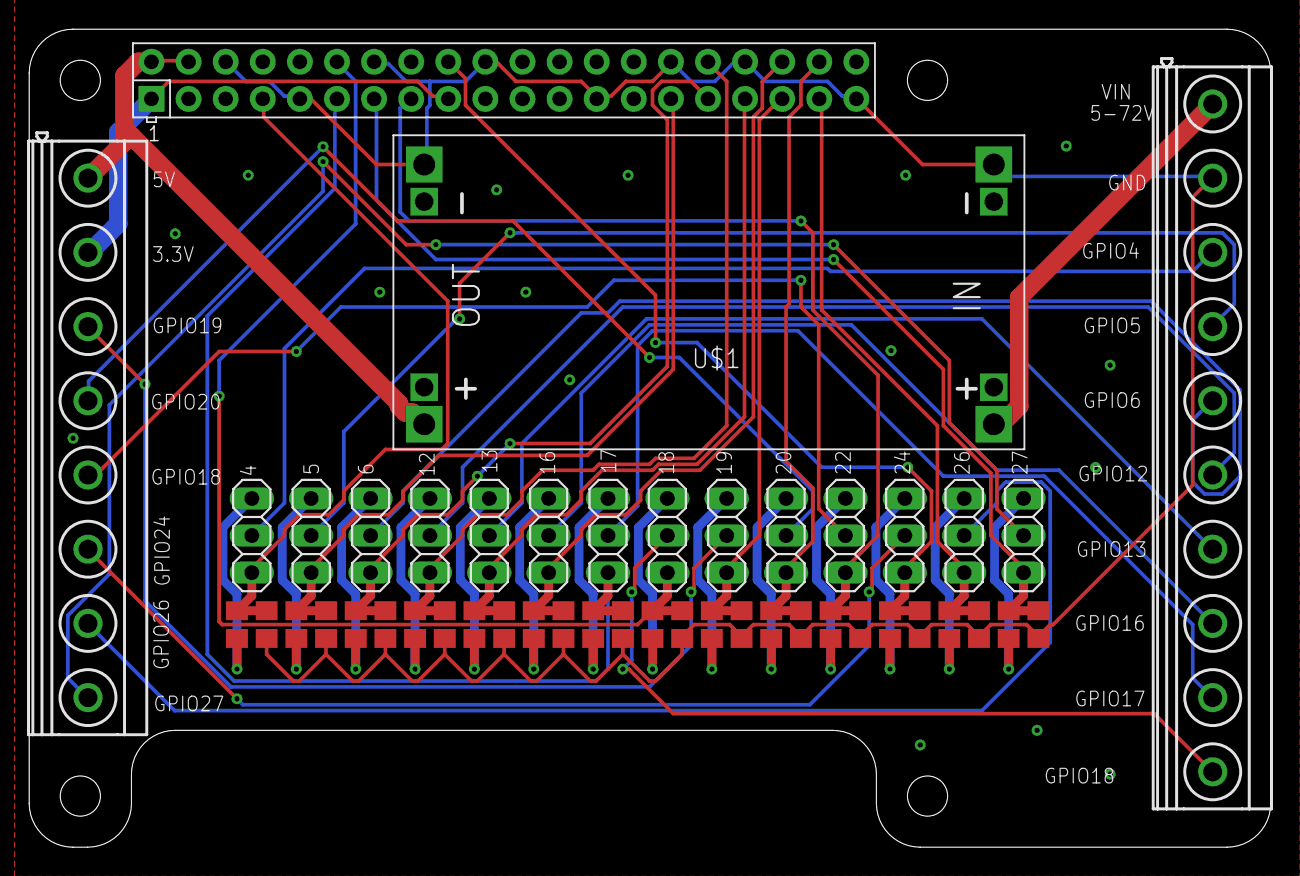
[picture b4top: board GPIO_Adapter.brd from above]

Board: 2 copper layers, 85.0 x 56.0 mm, 46 parts (0 on the bottom side), 46 nets.

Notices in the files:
parts and their libraries:
diy-modules: Released under the Creative Commons Attribution 4.0 International License: http://creativecommons.org/licenses/by/4.0
